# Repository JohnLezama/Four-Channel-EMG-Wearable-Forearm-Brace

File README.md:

# Four-Channel EMG Wearable Forearm Brace

**Status:** Functional four-channel acquisition prototype; grip classification and prosthetic control remain in development

**Project period:** Summer 2026

> This is an experimental engineering prototype, not a medical device. It is not intended for diagnosis, treatment, or unsupervised clinical use.

## 1. Project Overview and Current Result

Surface electromyography, or sEMG, measures the electrical activity associated with muscle contraction using electrodes placed on the skin. Many of the muscles responsible for hand movement are located in the forearm, making multi-channel forearm EMG a potential input for grip classification and prosthetic hand control.

The objective of this project was to develop a low-cost wearable system capable of acquiring four forearm EMG channels simultaneously while reducing noise.

I designed and fabricated:

* Four compact analog front-end PCBs
* A separate driven-right-leg feedback and voltage-reference PCB
* A 3D-printed forearm brace that houses:
  * Mounting for eight sensing electrodes and one reference electrode
  * All the PCBs and an ESP32

The current prototype acquires and displays four simultaneous EMG channels with observable responses to finger movements. It establishes the hardware foundation for collecting labeled grip data, training a classification model, and eventually controlling a prosthetic hand in real time.

## 2. Demonstration

https://github.com/user-attachments/assets/97304fc7-ee5d-449a-bffc-9f695163887c

The demonstration shows the completed brace acquiring four EMG channels while different grips are performed.

## 3. System Architecture

```mermaid
flowchart TD
    A["Eight sensing electrodes"] --> B["Four differential electrode pairs"]
    B --> C["Four INA351 instrumentation-amplifier stages"]
    C --> D["20 Hz high-pass filters"]
    D --> E["500 Hz low-pass filters"]
    E --> F["Final gain stages"]
    F --> G["ESP32 ADC inputs"]
    G --> H["Real-time serial visualization"]

    B --> I["Common-mode averaging network"]
    I --> J["Driven-reference and VREF board"]
    J --> K["Reference electrode"]
```

Each EMG channel follows the same analog signal path:

1. Two electrodes measure the differential voltage across a region of the forearm.
2. An INA351 instrumentation amplifier provides an initial gain of 20.
3. A 20 Hz high-pass stage attenuates baseline drift and low-frequency artifacts.
4. A 500 Hz low-pass stage attenuates higher-frequency interference.
5. A final non-inverting stage increases the signal amplitude for acquisition.
6. The output is sampled by the ESP32 and displayed in real time.

A separate board generates a mid-supply voltage reference and implements a driven-right-leg circuit that feeds back to the reference electrode. A resistor network estimates the common-mode component across the electrodes, and the feedback circuit drives the reference electrode to reduce common-mode interference.

## 4. My Contributions

This was an independent project. I was responsible for the complete hardware and software workflow, including:

* Researching surface-EMG acquisition, electrode placement, analog filtering, and driven-reference circuits
* Defining the electrical and mechanical requirements
* Designing and simulating the analog front end in KiCad
* Modeling realistic electrode signals and interference
* Designing the individual EMG-channel PCBs
* Designing the driven-reference and voltage-reference PCB
* Preparing and reviewing PCB fabrication files
* Selecting and soldering the surface-mount components
* Designing the forearm brace in Onshape
* Printing and evaluating electrode-fit prototypes
* Mounting nine electrodes and the associated PCBs
* Wiring the complete wearable system
* Programming the ESP32 in C++ for four-channel acquisition and visualization
* Performing frequency-response and live wearable testing
* Documenting the development and debugging process

https://github.com/user-attachments/assets/0f952d16-c39a-4ed7-ad40-192b02eae874

## 5. Design Requirements

| Requirement | Target | Current Status |
|---|---|---|
| Number of channels | Four simultaneous differential EMG channels | Demonstrated |
| Electrode count | Eight sensing electrodes and one reference electrode | Demonstrated |
| Target passband | Approximately 20–500 Hz | Simulated and bench-tested |
| Initial instrumentation gain | 20× per channel | Implemented |
| PCB size | Maximum of approximately 15 × 20 mm per channel board | Implemented |
| Electrode retention | Secure skin contact during hand movement | Implemented with fitted brace |
| Electrode opening | Fit the selected electrode hardware | Iterated to approximately 4.025 mm |
| Acquisition | Real-time four-channel display | Demonstrated |
| Wearability | Electronics mounted directly on the forearm | Functional prototype |
| Cost | Lower-cost alternative to commercial multi-channel EMG hardware | Final cost not yet calculated |
| Future compatibility | Produce data suitable for grip classification | Dataset and classifier not yet completed |

## 6. Major Design Decisions

### Four modular channel boards

I used four identical signal-conditioning PCBs rather than placing every channel on one large rigid board. This allowed the electronics to be distributed around the forearm, fit the brace geometry, and be tested or replaced one channel at a time.

### Differential instrumentation amplifier

Raw EMG signals are small and are easily overwhelmed by noise. The INA351 instrumentation amplifier was selected to amplify the signal due to its high common-mode rejection ratio.

### 20–500 Hz analog passband

The analog chain uses high-pass and low-pass filtering to retain the primary EMG frequency range while attenuating slow baseline drift, motion artifacts, and higher-frequency noise. Filtering before the ADC also reduces the amount of unwanted signal amplified by later stages.

### Driven-reference feedback

Power-line interference was a major concern because the body and electrode wires can couple environmental noise into every channel. I added a driven-reference circuit based on driven-right-leg topology to estimate the common-mode voltage and feed an inverted correction signal through the reference electrode.

The final board also generates the mid-supply voltage reference required for single-supply analog operation.

### Fixed electrode brace

Surface EMG is highly dependent on electrode position and skin contact. A wearable brace was used to keep the four electrode pairs in consistent locations while also carrying the circuitry.

### Electrode-fit coupon before the full brace

Instead of repeatedly printing the complete brace, I first created a small fitting test containing several electrode-hole diameters. This reduced print time and material use.

### 0805 surface-mount components

The PCBs needed to be small enough to fit the brace but practical enough to solder by hand. The selected component size balanced compactness with solderability.

### ESP32 acquisition

The ESP32 provided multiple ADC channels, C++ programmability, and a path toward future wireless telemetry and real-time prosthetic control.

## 7. Challenges, Failed Approaches, and Fixes

### Driven-reference implementation

**Problem:** I needed to incorporate driven-reference feedback into a four-channel system rather than treating each channel as an isolated circuit.

**Fix:** I designed a separate board that generated VREF and used a resistive averaging network connected to the sensing inputs to estimate the system’s common-mode voltage.

**Result:** The driven-reference circuit could be shared across all four sensing channels and connected to a single reference electrode.

### Electrode-hole sizing

**Problem:** The dimensions taken from the electrode hardware did not directly produce the desired printed fit.

**First approach:** I printed a fitting test with nominal openings of 3.575, 3.650, 3.725, 3.800, 3.875, 3.950, 4.025, and 4.100 mm.

**Fix:** Based on the physical test, I revised the opening to 4.025 mm.

**Result:** The revised geometry produced more secure and repeatable electrode retention in the completed brace.

### PCB area constraint

**Problem:** Each sensing board had to fit within an approximately 15 × 20 mm region of the brace.

**Fix:** I distributed the system across four identical channel boards and a separate driven-reference/VREF board. Component selection occurred after the mechanical envelope had been established.

**Result:** The fabricated electronics could be mounted directly on the wearable structure.

### Fabricated-board debugging

**Problem:** Debugging the complete output alone did not reveal which analog stage was responsible for an unexpected response.

**Fix:** I injected known signals with a function generator and recorded the outputs of the instrumentation-amplifier, filter, and final-gain stages separately. I tested the output at frequencies ranging from 1 Hz to 1 kHz.

**Result:** The node-by-node procedure made it possible to evaluate each stage independently and reveal a burnt chip from the low-pass filter stage.

## 8. Testing and Measurable Results

### Simulation testing

The analog front end was evaluated using:

* AC frequency sweeps
* Transient simulations
* Millivolt-scale differential inputs
* Simulated electrode impedances
* Driven-reference feedback
* A mid-supply voltage reference
* SPICE models for the respective ICs

The simulation demonstrated:

* A stable baseline around the mid-supply reference
* Amplification of the differential input
* Attenuation below the 20 Hz high-pass region
* Attenuation above the 500 Hz low-pass region
* An initial instrumentation-amplifier gain of 20

### Bench testing

The fabricated signal board was driven with known test signals at:

`1, 5, 10, 20, 30, 50, 100, 200, 300, 400, 500, 600, 800, and 1000 Hz`

Outputs were captured at the instrumentation-amplifier and final-output nodes. This provided evidence that the fabricated board responded across the intended EMG band and attenuated signals outside it.

### Mechanical testing

| Measurement                |                 Result |
| -------------------------- | ---------------------: |
| Sensing channels           |                      4 |
| Sensing electrodes         |                      8 |
| Reference electrodes       |                      1 |
| Total electrodes           |                      9 |
| Target PCB envelope        | 15 × 20 mm per channel |
| Selected electrode opening | Approximately 4.025 mm |

### Wearable demonstration

The completed system displayed four channels simultaneously while finger and hand movements were performed. Each channel showed observable changes during muscle activation.

The current demonstration establishes functional acquisition, but it does not yet provide formal measurements of:

* Signal-to-noise ratio
* Common-mode rejection improvement with and without driven feedback
* Channel crosstalk
* Session-to-session repeatability
* Electrode-placement sensitivity
* ADC accuracy or effective resolution
* Sampling latency
* Grip-classification accuracy

These measurements are planned for the next development phase.

## 9. Repository Guide

```text
Four-Channel-EMG-Wearable-Forearm-Brace/
├── CAD/
│   ├── ForearmBrace - FittingTest.stl
│   └── ForearmBrace.stl
├── Docs/
│   ├── Simulation/
│   │   ├── FrequencyPlot.png
│   │   ├── Input.png
│   │   ├── InputAndOutputTransientSimulationWithDRL.png
│   │   ├── SimulationSetup.png
│   │   ├── TestSchematic.png
│   │   └── VOUT.png
│   ├── Testing/
|   |   ├── FrequencyAmplitudes/
│   │   |   ├── OUT_1000Hz.png
│   │   |   ├── OUT_100Hz.png
│   │   |   ├── OUT_10Hz.png
│   │   |   ├── OUT_1Hz.png
│   │   |   ├── OUT_200Hz.png
│   │   |   ├── OUT_20Hz.png
│   │   |   ├── OUT_300Hz.png
│   │   |   ├── OUT_30Hz.png
│   │   |   ├── OUT_400Hz.png
│   │   |   ├── OUT_500Hz.png
│   │   |   ├── OUT_50Hz.png
│   │   |   ├── OUT_5Hz.png
│   │   |   ├── OUT_600Hz.png
│   │   |   └── OUT_800Hz.png
│   └── parts-list.md
├── Electronics/
│   ├── DRL&VREF/
│   │   ├── PCB/
│   │   |   └── DRL&VREF_V1.zip
│   │   ├── DRL&VREF.kicad_pcb
│   │   ├── DRL&VREF.kicad_pro
│   │   ├── DRL&VREF.kicad_sch
│   │   └── DRL&VREFSchematicScreenshot.png
│   ├── EMG-Channel/
│   │   ├── PCB/
│   │   |   └── EMGPCB_V2.zip
│   │   ├── EMGMain.kicad_pcb
│   │   ├── EMGMain.kicad_pro
│   │   ├── EMGMain.kicad_sch
│   │   └── EMGMainSchematicScreenshot.png
├── Firmware/
|   ├── EMG_SD_Data_Collection.ino
│   └── EMGDemo.ino
├── Media/
│   ├── ForearmBraceTop.jpg
│   ├── FrequencyPlot.png
│   └── InputAndOutputTransientSimulationWithDRL.png
├── README.md
└── References.md
```

### Directory descriptions

- `Firmware/` contains the ESP32 data-acquisition firmware.
- `CAD/` contains the printable brace models.
- `Electronics/` contains the KiCad source files, schematic images, PCB layouts, and Gerber packages.
- `Docs/Simulation/` contains frequency-response and transient-analysis results.
- `Docs/Testing/` contains injected-frequency captures and debugging evidence.
- `Docs/parts-list.md` contains the project bill of materials.
- `Media/` contains the images used in this README.
- `References.md` contains research papers and technical resources consulted during development.

Research papers should be linked or cited rather than redistributed unless their licenses permit redistribution.

## 10. How to Reproduce or Run It

### Safety warning

This is body-connected experimental electronics. Clinical biopotential systems use power and data isolation to limit leakage and ground-loop currents. This prototype has not been evaluated against medical electrical-safety standards.

When electrodes are attached:

* Use an isolated battery power source.
* Do not connect the system to mains-powered bench equipment.
* Disconnect the electrodes before charging, soldering, or probing the circuit.
* Prefer wireless telemetry over a wired connection to a mains-powered computer.
* Do not use the device for diagnosis, treatment, or testing on other people without qualified supervision.

For background on isolation in patient-connected electronics, see Texas Instruments’ [patient-monitor isolation guidance](https://www.ti.com/lit/an/sloa285a/sloa285a.pdf).

### Required hardware

* Four assembled EMG-channel PCBs
* One assembled driven-reference/VREF PCB
* ESP32
* Nine 3M Red Dot 2560 sensing electrodes
* Printed forearm-brace components
* Battery power source: 9V Battery
* Wiring, connectors, and mounting hardware

### Build procedure

1. Fabricate four copies of the EMG-Channel board using `Electronics/EMG-Channel/PCB/EMGPCB_V2.zip`.
2. Fabricate the driven-reference/VREF board using `Electronics/DRL&VREF/PCB/DRL&VREF_V1.zip`.
3. Assemble the PCBs according to the schematics and parts list.
4. Verify power, ground, and VREF before connecting electrodes or the ESP32.
5. Inject a small known test signal and confirm the output of every analog stage.
6. Print the brace from `CAD/`.
7. Install four differential electrode pairs and the reference electrode.
8. Mount the four channel boards and the driven-reference board on the brace.
9. Connect the channel outputs to the selected ESP32 ADC pins.
10. Integrate a compact onboard battery and wireless telemetry for safer, less restrictive wearable testing.11. Upload the code in `Firmware/`.
12. Open the specified serial plotting application and set the baud rate to 9600.
13. Establish a resting baseline before performing hand or finger movements.

The ESP32’s usable ADC range depends on its specific variant and attenuation configuration. Document the final voltage-scaling circuit and verify it against the appropriate [Espressif ADC documentation](https://docs.espressif.com/projects/esp-idf/en/v4.4.7/esp32/api-reference/peripherals/adc.html).

## 11. Current Limitations and Next Steps

Development is currently paused during my transition to UT Austin. I plan to resume the project using university maker-space resources and, if possible, research mentorship.

### Current limitations

* No labeled multi-grip dataset has been collected.
* No classification model has been trained or evaluated.
* Signal-to-noise ratio and common-mode rejection have not been quantified.
* The effect of electrode-position variation has not been measured.
* Testing has primarily been performed on a single user.
* The exposed wiring and separate boards are not yet packaged for long-term wearable use.
* The ESP32 sampling rate, ADC configuration, and voltage scaling need to be formally documented.
* The system has not been evaluated for medical safety or clinical use.
* Total system cost has not yet been calculated.
* Long-session comfort and electrode contact stability have not been evaluated.

### Next steps

1. Finalize the ESP32 acquisition code and document the sampling configuration.
2. Verify ADC input scaling and add protection or an external ADC if necessary.
3. Quantify the noise floor, signal-to-noise ratio, common-mode rejection, and channel crosstalk.
4. Design a repeatable electrode-placement and calibration procedure.
5. Record labeled data for several hand grips across multiple sessions.
6. Establish simple classification baselines before comparing them with a neural network.
7. Evaluate classification accuracy, confusion between grips, and real-time latency.
8. Integrate the classifier with a motorized prosthetic hand.
9. Replace temporary wiring with a more robust harness or consolidated PCB revision.
10. Add battery power and wireless telemetry for safer, less restrictive wearable testing.
11. Evaluate the system across additional users only under appropriate supervision and safety controls.
12. Compare the total cost and performance with existing commercial EMG systems.

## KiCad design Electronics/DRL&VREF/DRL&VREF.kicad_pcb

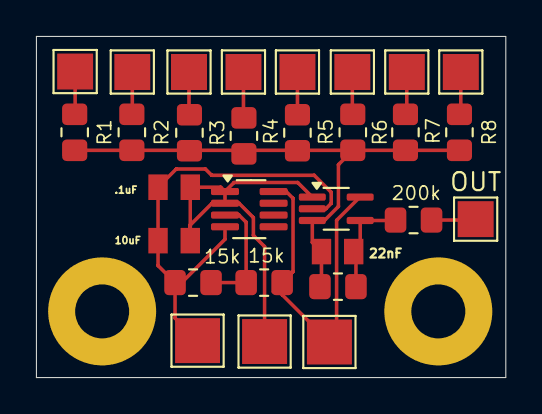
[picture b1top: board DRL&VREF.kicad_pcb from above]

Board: 2 copper layers, 26.1 x 18.9 mm, 29 parts (0 on the bottom side), 15 nets.

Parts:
10uF, 22nF, .1uF: c=GCM21B5C1H223FA16L; CAPC2012X140N
15k, 15k#2: 15k; R_0805_2012Metric_Pad1.20x1.40mm_HandSolder
200k: 200k; R_0805_2012Metric_Pad1.20x1.40mm_HandSolder
E1, E2, E3, E4: Conn_01x01_Pin; TestPoint_Pad_2.0x2.0mm
E'1, E'2, E'3, E'4: Conn_01x01_Pin; TestPoint_Pad_2.0x2.0mm
GND: Conn_01x01_Pin; TestPoint_Pad_2.5x2.5mm
OUT: Conn_01x01_Pin; TestPoint_Pad_2.0x2.0mm
R1, R2, R3, R4, R5, R6, R7, R8: 12k; R_0805_2012Metric_Pad1.20x1.40mm_HandSolder
R10: 75k; R_0805_2012Metric_Pad1.20x1.40mm_HandSolder
U1: OPA333xxDCK; SOT-353_SC-70-5_Handsoldering
U2: TL072; SOT-23-8_Handsoldering
VREF: Conn_01x01_Pin; TestPoint_Pad_2.5x2.5mm
VS: Conn_01x01_Pin; TestPoint_Pad_2.5x2.5mm

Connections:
unnamed: 22nF.2, 200k.2, R10.1, U1.4
unnamed: E1.1, R1.1
unnamed: E2.1, R3.1
unnamed: E3.1, R5.1
unnamed: E4.1, R7.1
unnamed: E'1.1, R2.1
unnamed: E'2.1, R4.1
unnamed: E'3.1, R6.1
unnamed: E'4.1, R8.1
unnamed: 10uF.2, 15k.2, .1uF.2, GND.1, U1.2 (V-), U2.4 (V-)
unnamed: 200k.1, OUT.1
unnamed: 10uF.1, .1uF.1, U1.1 (+), U2.1, U2.2 (-), VREF.1
unnamed: 22nF.1, R1.2, R2.2, R3.2, R4.2, R5.2, R6.2, R7.2, R8.2, R10.2, U1.3 (-)
unnamed: 15k#2.1, U1.5 (V+), U2.8 (V+), VS.1
unnamed: 15k.1, 15k#2.2, U2.3 (+)
